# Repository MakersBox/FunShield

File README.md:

**The FunShield was designed and produced by:**
> Ken Olsen
> 648.ken@gmail.com
> MakersBox.blogspot.com

The FunShield is an Arduino shield that provides a variety of inputs and outputs for you quickly access. The use of library functions further simplifies the programming experience for beginners. Dedicated pin assignments also facilitate the combination of inputs and outputs in projects without conflicts.

**To use the library**, download and unzip the folder.  Copy the "FunShield-master\FunShield\libraries\FunShield" folder into the "library" folder of your sketchbook. Restart your Arduino IDE and "FunShield" should show up under [File] -> [Examples].
	
**Initializing the FunShield**

    #include <FunShield.h>
    FunShield fs;   // This gives us access to FunShield functions using "fs"

**LEDs**
The FunShield uses an 74HC595N shift register to control eight LEDs using only three pins on the Arduino.  LEDs are numbered from 0 on the left to 7 on the right (ignore PCB markings). The FunShield library abstracts the details and provides you the following function:
  
    LED(led, state); // led is a number between 0 and 7.
                     // HIGH to turn on or LOW to turn off.

**RGB LED**
The FunShield uses a common cathode RGB LED to display a spectrum of colors.
The FunShield library abstracts the details and provides you the following function:
  
    RGB(RGBcolor);   // Where RGBcolor is an array of the 
                     // three color components like
                     // byte RED[] = {255, 0, 0} or 
                     // an integer between 0 and 767 to display a
                     // color on the spectrum.

**Buttons**
The FunShield has two buttons connected to D7 & D8. The FunShield library abstracts the  details and provides  you the following function:

  button(side);      // returns button state (true if pressed) for given side (LEFT or RIGHT)
                     // LEFT = false, RIGHT = true
The shield also has a touch pad attached to pin A3 and will return true if touched: 

    touch();         // returns true if touched (analog < 1000) 

**Analog Input**
The FunShield has the following analog inputs:

    trim();   // returns a 10-bit reading from the potentiometer   
    light();  // returns a 10-bit reading from the photo cell
    analog(); // returns a 10-bit reading from "ANL" header (same as touch sensor)
    temp();   // returns temperature as a float in Celsius

**Sound**
The FunShield uses piezo speaker attached to pin D1.

    speaker(frequency, duration); // frequency in hertz, duration in milliseconds.

**Motor**
The FunShield has an NPN transistor gate connected to pin D3. Suppling a signal to the   transistor allows current to flow through it. This allows us to supply more current to a device (like a motor) than the digital pin can supply alone (only 40 mA). The current limit to the device is dependent on the transistor, usually 500 mA, or enough to power a small hobby motor. Be careful, as the transistor can get hot! 
See http://arduino.cc/en/Tutorial/PWM to learn how PWM controls speed.
    
	motor(pmw_value);         // can be a value between 0 (OFF) and 255 (100% PWM).
	
**I2C**
The FunShield has two mirrored I2C connection on the right side of the board. This allows it to communicate to other devices using the Wire library. Each device must have an unique 7-bit address number. 

    #define ME 20             // this shield's I2C address
    #define FRIEND 21         // connected shield's I2C address
    FunShield fs(ME, FRIEND); // This initializes board and pins

Each of the following functions work by prefacing arguments with an address of the connected FunShield:
  
    LED(address, led, state);
    RGB(address, color);
    speaker(address, frequency, duration);
    motor(speed);

The base LED() fuction will also send an led > 7 to the opposite boards led from highest to lowest (i.e. 15 - led).

    LED(14, HIGH);         // lights LED 1 on attached FunShield
    
You can also access sensor and button values from the other board:
    
    light(address);        // returns light value from other board
    trim(address);
    button(address, side);

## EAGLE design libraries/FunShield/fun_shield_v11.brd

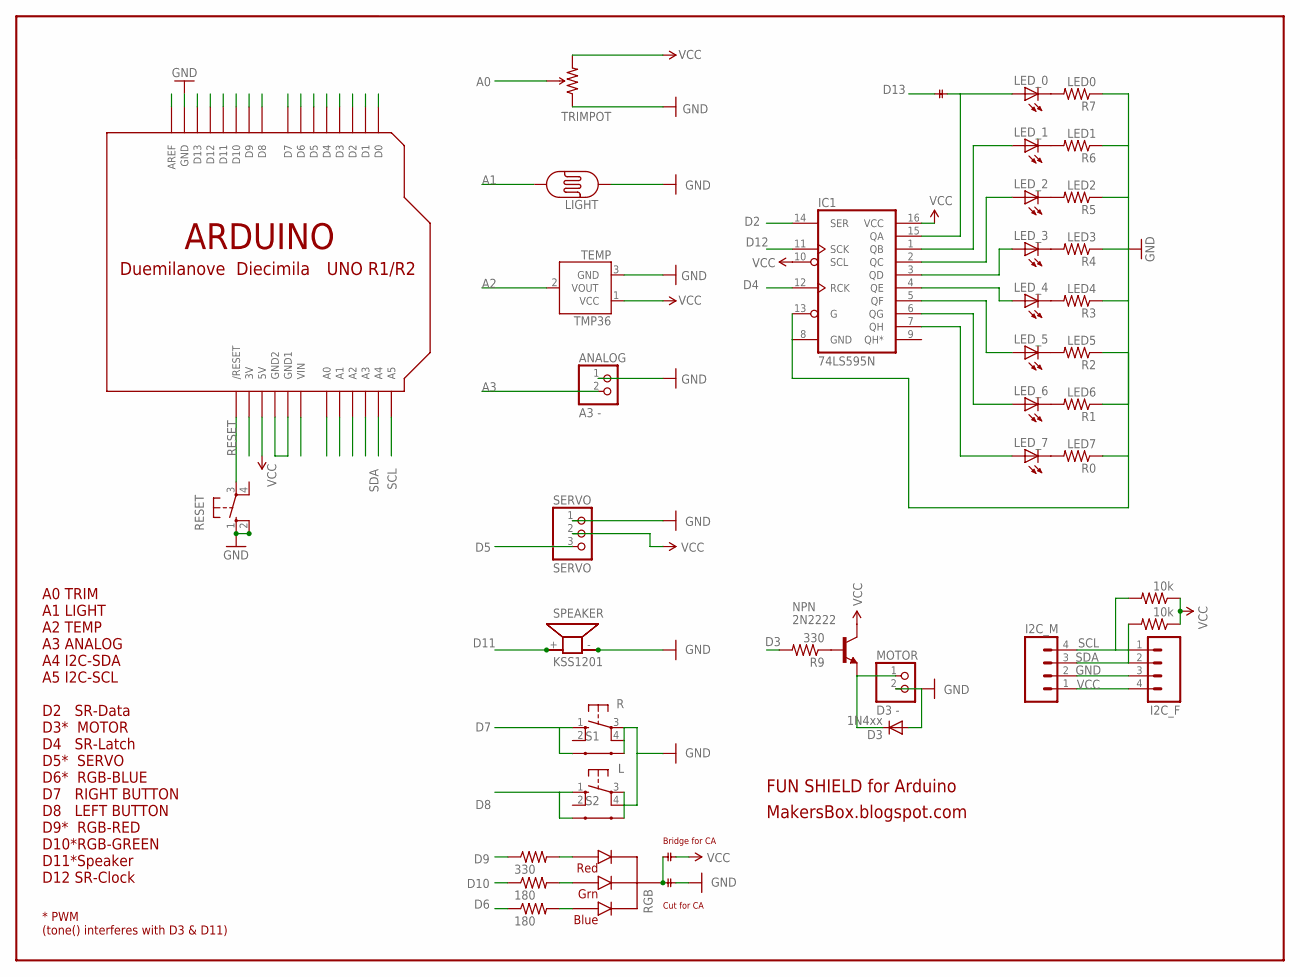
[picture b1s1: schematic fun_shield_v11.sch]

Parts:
ANALOG: A3 -; 1X02
D3: 1N4xx; DIODE-1N4148
I2C_F, I2C_M: M04PTH; 1X04
IC1: 74LS595N; DIL16
L: 10-XX; B3F-10XX
LED_0, LED_1, LED_2, LED_3, LED_4, LED_5, LED_6, LED_7: LED5MM
LIGHT: PHOTOCELLPTH; PHOTOCELL
MOTOR: D3 -; 1X02
NPN: 2N2222; TO92-EBC-OVAL
R: 10-XX; B3F-10XX
R0: LED7; 0204/7
R1: LED6; 0204/7
R2: LED5; 0204/7
R3: LED4; 0204/7
R4: LED3; 0204/7
R5: LED2; 0204/7
R6: LED1; 0204/7
R7: LED0; 0204/7
R8, R9: 330; 0204/7
R11, R12: 180; 0204/7
R16, R17: 10k; 0204/7
RESET: 10-XX; B3F-10XX
RGB: RGBLED_CC; LED5MMRGB
S1, S2: SWITCH-MOMENTARY-2-CLOSED; TACTILE-PTH-12MM
SERVO: SERVO; 1X03
SP1: KSS1201
SPEAKER: SPEAKER/PS12; PS12
TMP36: TEMP; TO-92-AMMO
TRIMPOT: TRIMPOT; 3362U
U$1: CUT
U$2, U$3: CUT_NOT
U$5: ARDUINO-NOHOLE

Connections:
A0: TRIMPOT.P$2 (WIPER), TRIMPOT.P$4 (WIPER), U$5.A0
A1: LIGHT.2, U$5.A1
A2: TMP36.2 (VOUT), U$5.A2
A3: ANALOG.2, U$5.A3
BLUE: R12.2, RGB.4 (BLUE)
D0: U$5.D0
D1: U$5.D1
D2: IC1.14 (SER), U$5.D2
D3: R9.2, U$5.D3
D4: IC1.12 (RCK), U$5.D4
D5: SERVO.3, U$5.D5
D6: R12.1, U$5.D6
D7: R.1 (S), S1.1, U$5.D7
D8: L.1 (S), S2.1, U$5.D8
D9: R8.1, U$5.D9
D10: R11.1, U$5.D10
D11: SP1.+ (1), SPEAKER.P$1 (+), U$5.D11
D12: IC1.11 (SCK), U$5.D12
D13: IC1.15 (QA), LED_0.A, U$3.P$1, U$3.P$2, U$5.D13
GND: ANALOG.1, D3.A, I2C_F.3, I2C_M.2, IC1.8 (GND), IC1.13 (G), L.3, L.4 (P1), LIGHT.1, MOTOR.2, R.3, R.4 (P1), R0.1, R1.1, R2.1, R3.1, R4.1, R5.1, R6.1, R7.1, RESET.1 (S), RESET.2 (S1), S1.3 (2), S2.3 (2), SERVO.1, SP1.- (2), SPEAKER.P$2 (-), TMP36.3 (GND), TRIMPOT.P$1 (CCW), U$2.P$2, U$5.GND, U$5.GND1, U$5.GND2
GRN: R11.2, RGB.3 (GREEN)
unnamed: LED_6.K (C), R1.2
unnamed: LED_5.K (C), R2.2
unnamed: LED_4.K (C), R3.2
unnamed: LED_3.K (C), R4.2
unnamed: LED_2.K (C), R5.2
unnamed: LED_1.K (C), R6.2
unnamed: LED_0.K (C), R7.2
unnamed: LED_7.K (C), R0.2
unnamed: IC1.1 (QB), LED_1.A
unnamed: IC1.2 (QC), LED_2.A
unnamed: IC1.3 (QD), LED_3.A
unnamed: IC1.4 (QE), LED_4.A
unnamed: IC1.5 (QF), LED_5.A
unnamed: IC1.6 (QG), LED_6.A
unnamed: IC1.7 (QH), LED_7.A
unnamed: D3.C, MOTOR.1, NPN.E
unnamed: RGB.2 (GND), U$1.P$1, U$2.P$1
unnamed: NPN.B, R9.1
RED: R8.2, RGB.1 (RED)
RESET: RESET.3, U$5.RESET (/RESET)
SCL: I2C_F.1, I2C_M.4, R17.2, U$5.A5
SDA: I2C_F.2, I2C_M.3, R16.2, U$5.A4
VCC: I2C_F.4, I2C_M.1, IC1.10 (SCL), IC1.16 (VCC), NPN.C, R16.1, R17.1, SERVO.2, TMP36.1 (VCC), TRIMPOT.P$3 (CW), U$1.P$2, U$5.5V, U$5.AREF
VIN: U$5.VIN

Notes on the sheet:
FUN SHIELD for Arduino
MakersBox.blogspot.com
A0 TRIM A1 LIGHT A2 TEMP A3 ANALOG A4 I2C-SDA A5 I2C-SCL D2 SR-Data D3* MOTOR D4 SR-Latch D5* SERVO D6* RGB-BLUE D7 RIGHT BUTTON D8 LEFT BUTTON D9* RGB-RED D10*RGB-GREEN D11*Speaker D12 SR-Clock
* PWM (tone() interferes with D3 & D11)
Bridge for CA
Cut for CA

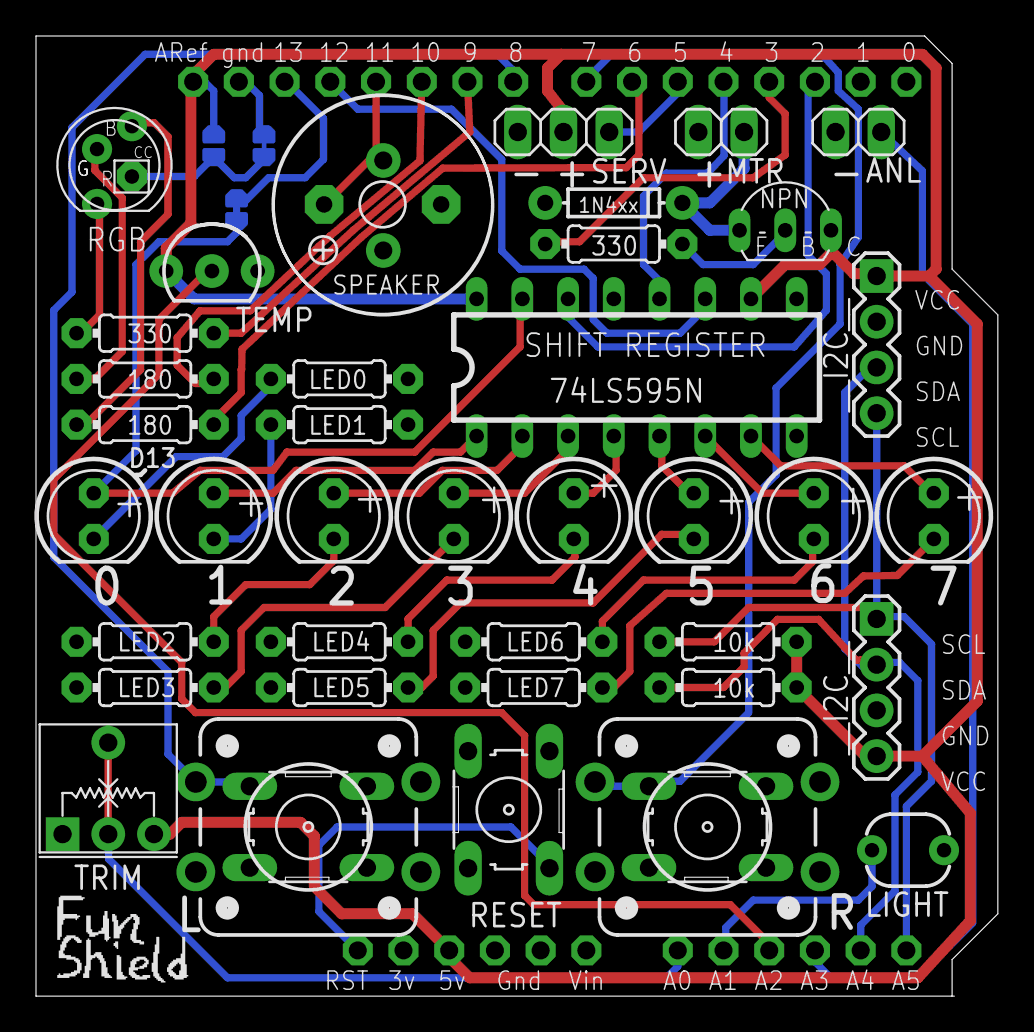
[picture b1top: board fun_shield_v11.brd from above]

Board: 2 copper layers, 53.4 x 53.3 mm, 50 parts (0 on the bottom side), 42 nets.

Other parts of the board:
U$4: FUN_SHEILD_22
U$6: MB_02_22
U$7: OREGON_REV_035
U$8: FUN_SHIELD_03_300
U$9: OSHWLOGO_BOTTOM

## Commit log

2014-04-11 adding ArduBlock examples
2019-05-09 Update for newer Arduino version.

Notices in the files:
parts and their libraries:
SparkFun: Licensing: CC v3.0 Share-Alike You are welcome to use this library for commercial purposes.
SparkFun-Electromechanical: Licensing: Creative Commons ShareAlike 4.0 International - https://creativecommons.org/licenses/by-sa/4.0
